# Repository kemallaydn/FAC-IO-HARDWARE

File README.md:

# FAC-IO Mini V1 — Ethernet Barrier Relay Controller

Status: **Integrated engineering draft. NOT production-ready.** KiCad 10.0.8 ERC/DRC and schematic parity currently pass; sourcing, mechanical, supplier, independent review, and first-article gates remain open.

FAC-IO is an Ethernet-connected, programmable dry-contact relay controller for integration with our own license-plate recognition/access-control software. It is **not** a barrier motor driver.

## V1 scope
- ESP32-C3-WROOM-02-N4 in current DRAFT BOM (GPIO/USB and antenna placement still require physical review)
- WIZnet WIZ850io (W5500 + PHY + magnetics + RJ45) as a plug-in module on two host sockets
- 2 independent, normally-open / common / normally-closed dry-contact relay outputs
- 12 V DC input, regulated 3.3 V logic supply
- USB programming/debug interface, BOOT/RESET recovery access
- Power, link and relay indicators; four mounting holes
- Firmware source contains DHCP and an HMAC-authenticated fixed-pulse command path; a host signer/client exists, but LPR integration, Secure Boot/flash-encryption production build and target verification are incomplete, so command service remains fail-closed in the current build
- Two independent hardware one-shots nominally limit OPEN/CLOSE relay pulses to about 503 ms; tolerance and fail-safe behavior still require first-article validation
- Optional future PoE; **not included** in V1
- RS232, RS485 and legacy Nöron protocol **not required** in V1

## System flow
LPR service -> authenticated LAN command -> FAC-IO -> timed dry-contact closure -> barrier controller OPEN or CLOSE input.

The dry-contact output must be wired only to the barrier controller's documented command input, **never directly to the motor or mains**. Each channel uses a fixed hardware one-shot (about 503 ms nominal from the current timer/resistor values); firmware cannot extend or configure the relay pulse. The full pulse tolerance and first-article maximum still require verification.

Hikvision's 42-Series brochure identifies the third-party command interfaces as **Rising Control ±** and **Falling Control ±**; it does not substantiate controller terminal numbers such as J4/J5. Wire each isolated relay COM/NO pair only across the matching, physically labelled command pair. Hikvision states that closing accepts pulsed signals only and a continuous closing signal can lock the barrier. The independent hardware one-shot bounds both outputs, but the nominal 503 ms pulse and its maximum tolerance must be verified on the exact controller revision before connection. Do not connect FAC-IO power or ground to these pairs. Never connect to mains, motor or traffic-light terminals. ([Hikvision 42-Series brochure](https://www.hikvision.com/content/dam/hikvision/en/brochures-download/product-brochures/Leaflet--Barrier-Gate-42-Series.pdf))

## Repository layout
- `docs/requirements.md`: engineering requirements and open decisions
- `docs/validation.md`: verification and acceptance plan
- `hardware/`: integrated KiCad schematic, PCB and local footprints
- `manufacturing/`: draft Gerber, Excellon, BOM, positions and validation artifacts
- `firmware/`: ESP32-C3/W5500 candidate firmware, protocol/security implementation and host tests; development target build passes, while production-secure build and first-article validation remain open

## Manufacturing release rule
The current-source bare-board review bundle is `manufacturing/REVIEW-2026-11-10-DRAFT/`; it contains fresh Gerber/Excellon outputs, current ERC/DRC reports, a preview and hashes. It includes `release/NOT-APPROVED.txt` and is not approved for fabrication. The package gate with `--root` currently reports only the missing independent approval file. CAM/stackup and drill/slot acceptance, Robotistan pricing/acceptance, module/header fit, independent electrical review and first-article tests remain open. `manufacturing/release_check.py` is the release gate.

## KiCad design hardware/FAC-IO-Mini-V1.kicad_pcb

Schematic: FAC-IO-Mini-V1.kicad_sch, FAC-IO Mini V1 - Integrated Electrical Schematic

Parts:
C1: 22uF/50V; C_1210_3225Metric; MPN C3225X7R1H226M250AC
C2: 10uF/50V; C_1206_3216Metric; MPN CGA5L1X7R1H106K160AC
C3: 100nF/50V; C_0603_1608Metric; MPN CC0603JRX7R9BB104
C4, C5: 22uF/10V; C_0805_2012Metric; MPN GRM21BZ71A226ME15L
C6: 1uF; C_0805_2012Metric; MPN GRM21BR71C105KA01L
C7: 10uF; C_0805_2012Metric; MPN GRM21BZ71E106KE15L
C8, C30: 100nF; C_0603_1608Metric; MPN CC0603JRX7R9BB104
C9: 1nF/2kV; C_1206_3216Metric; MPN CC1206KKX7RDBB102
C28, C29: 100nF/100V; C_0805_2012Metric; MPN C0805C104K1RACAUTO
D1: SS34; D_SMA; MPN B340A-13-F
D2: SMCJ15A-13-F; D_SMC; MPN SMCJ15A-13-F
D3, D4: 1N4007G; D_DO-41_SOD81_P10.16mm_Horizontal; MPN 1N4007G-T
F1: 1812L075/33DR; Fuse_1812_4532Metric; MPN 1812L075/33DR
J1: TB007-508-02BE; TerminalBlock_CUI_TB007-508-02_1x02_P5.08mm_Horizontal; MPN TB007-508-02BE
J2: TYPE-C-31-M-12; USB_C_Receptacle_HRO_TYPE-C-31-M-12; MPN TYPE-C-31-M-12
J4, J5: TB007-508-03BE; TerminalBlock_CUI_TB007-508-03_1x03_P5.08mm_Horizontal; MPN TB007-508-03BE
J6: SSQ-106-03-G-S; WIZ850io_Host_J1_Socket_1x06; MPN SSQ-106-03-G-S
J7: SSQ-106-03-G-S; WIZ850io_Host_J2_Socket_1x06; MPN SSQ-106-03-G-S
K1, K2: G6K-2P-Y DC12; Relay_DPDT_Omron_G6K-2P-Y; MPN G6K-2P-Y DC12
L1: XAL5050-472MEC; L_Coilcraft_XAL5050-XXX; MPN XAL5050-472MEC
PWR1, PWR2, PWR3, PWR5: PWR_FLAG
Q1, Q2: AO3400A; SOT-23; MPN AO3400A
R1, R2, R10, R11, R12: 10k; R_0603_1608Metric; MPN RC0603FR-0710KL
R3, R4: 5.1k; R_0603_1608Metric; MPN RC0603FR-075K1L
R5, R6: 22R; R_0603_1608Metric; MPN RC0603FR-0722RL
R7: 68k; R_0603_1608Metric; MPN RC0603FR-0768KL
R8, R20, R21, R26, R28: 100k; R_0603_1608Metric; MPN RC0603FR-07100KL
R23, R24: 768k; R_0603_1608Metric; MPN RC0603FR-07768KL
R25, R27: 1k; R_0603_1608Metric; MPN RC0603FR-071KL
R29: 1M; R_0603_1608Metric; MPN RC0603FR-071ML
R30: 523k; R_0603_1608Metric; MPN RC0603FR-07523KL
SW1: RESET; SW_SPST_TL3342; MPN TL3342F100QG
SW2: BOOT; SW_SPST_TL3342; MPN TL3342F100QG
U1: AP63203WU-7; TSOT-23-6; MPN AP63203WU-7
U2: ESP32-C3-WROOM-02-N4; ESP32-C3-WROOM-02_0p3mmThermal; MPN ESP32-C3-WROOM-02-N4
U3: USBLC6-2SC6; SOT-23-6; MPN USBLC6-2SC6
U5, U6: LTC6993IS6-1; TSOT-23-6; MPN LTC6993IS6-1#TRMPBF

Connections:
/3V3: C4.1, C5.1, C7.1, C8.1, C28.1, C29.1, C30.1, J7.2, J7.3, L1.2, PWR3.1, R1.1, R2.1, R10.1, R11.1, R12.1, R29.1, U1.1 (FB), U2.1 (3V3), U5.5 (V+), U6.5 (V+)
/12V_FUSED: D1.2 (A), F1.2
/12V_IN: F1.1, J1.1, PWR1.1
/12V_PROT: C1.1, C2.1, D1.1 (K), D2.1 (K), D3.1 (K), D4.1 (K), K1.A1, K2.A1, PWR2.1, U1.2 (EN), U1.3 (IN)
/BOOT_N: R2.2, SW2.1, U2.8 (IO9)
/BUCK_BST: C3.1, U1.6 (BST)
/BUCK_SW: C3.2, L1.1, U1.5 (SW)
/CHASSIS: C9.1, J2.SH (SHIELD)
/CLOSE_COM: J5.2, K2.11
/CLOSE_NC: J5.1, K2.12
/CLOSE_NO: J5.3, K2.14
/COIL1_LOW: D3.2 (A), K1.A2, Q1.3 (D)
/COIL2_LOW: D4.2 (A), K2.A2, Q2.3 (D)
/ESP_EN: C6.1, R1.2, SW1.1, U2.2 (EN)
/ETH_CS_N: J6.5, R10.2, U2.6 (IO7)
/ETH_INT_N: J6.6, R11.2, U2.10 (IO10)
/ETH_MISO: J7.6, U2.5 (IO6)
/ETH_MOSI: J6.3, U2.4 (IO5)
/ETH_RESET_N: J7.5, R12.2, U2.15 (IO3)
/ETH_SCK: J6.4, U2.3 (IO4)
/GATE1: Q1.1 (G), R25.2, R26.1
/GATE2: Q2.1 (G), R27.2, R28.1
/GND: C1.2, C2.2, C4.2, C5.2, C6.2, C7.2, C8.2, C9.2, C28.2, C29.2, C30.2, D2.2 (A), J1.2, J2.A1 (GND), J2.A12 (GND), J2.B1 (GND), J2.B12 (GND), J6.1, J6.2, J7.1, PWR5.1, Q1.2 (S), Q2.2 (S), R3.2, R4.2, R8.2, R20.2, R21.2, R23.2, R24.2, R26.2, R28.2, R30.2, SW1.2, SW2.2, U1.4 (GND), U2.9 (GND), U2.19 (GND), U3.2 (GND), U5.2 (GND), U6.2 (GND)
/OPEN_COM: J4.2, K1.11
/OPEN_NC: J4.1, K1.12
/OPEN_NO: J4.3, K1.14
/PULSE1: R25.1, U5.6 (OUT)
/PULSE2: R27.1, U6.6 (OUT)
/SET1: R23.1, U5.3 (SET)
/SET2: R24.1, U6.3 (SET)
/TIMER_DIV: R29.2, R30.1, U5.4 (DIV), U6.4 (DIV)
/TRIG1: R20.1, U2.18 (IO0), U5.1 (TRIG)
/TRIG2: R21.1, U2.17 (IO1), U6.1 (TRIG)
/USB_CC1: J2.A5 (CC1), R3.1
/USB_CC2: J2.B5 (CC2), R4.1
/USB_DM: R6.2, U2.13 (IO18)
/USB_DM_CONN: J2.A7 (D-), J2.B7 (D-), R6.1, U3.3 (I/O2), U3.4 (I/O2)
/USB_DP: R5.2, U2.14 (IO19)
/USB_DP_CONN: J2.A6 (D+), J2.B6 (D+), R5.1, U3.1 (I/O1), U3.6 (I/O1)
/USB_VBUS: J2.A4 (VBUS), J2.A9 (VBUS), J2.B4 (VBUS), J2.B9 (VBUS), R7.1, U3.5 (VBUS)
/USB_VBUS_SENSE: R7.2, R8.1, U2.12 (IO21/TXD)

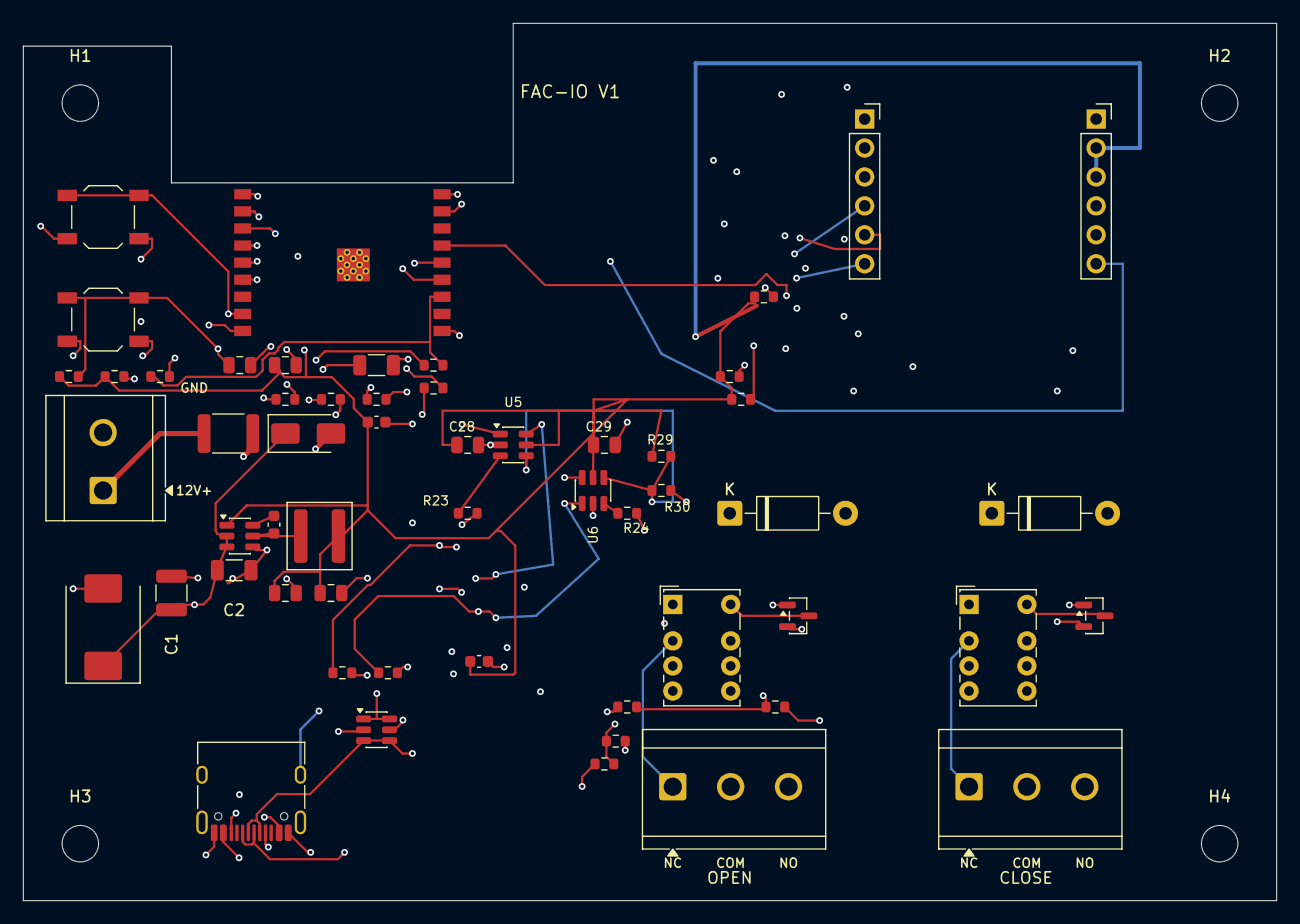
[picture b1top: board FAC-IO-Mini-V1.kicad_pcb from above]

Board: 4 copper layers, 110.0 x 77.0 mm, 60 parts (0 on the bottom side), 41 nets.

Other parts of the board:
H1, H2, H3, H4: MountingHole_3.2mm_M3

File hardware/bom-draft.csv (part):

Reference,Quantity,Value,Footprint,Manufacturer MPN,RobotistanPro/LCSC C Code,Populate,Status
C1,1,22uF/50V,Capacitor_SMD:C_1210_3225Metric,C3225X7R1H226M250AC,,YES,TDK 22uF/50V X7R 1210; input-bank DC-bias/temp/tolerance calculation and supplier availability remain to confirm
C2,1,10uF/50V,Capacitor_SMD:C_1206_3216Metric,CGA5L1X7R1H106K160AC,,YES,TDK 10uF/50V X7R 1206; input-bank DC-bias/temp/tolerance calculation and supplier availability remain to confirm
C3,1,100nF/50V,Capacitor_SMD:C_0603_1608Metric,C1608X7R1H104K080AA,C72453,YES,"TDK active-production 100nF 50V X7R 0603; LCSC C72453 matches exact MPN; supply, stock and assembly acceptance remain open"
C4,1,22uF/10V,Capacitor_SMD:C_0805_2012Metric,GRM21BZ71A226ME15L,C907991,YES,"LCSC code C907991 maps to exact manufacturer MPN GRM21BZ71A226ME15L; current stock, Robotistan procurement import and assembly acceptance remain unverified"
C5,1,22uF/10V,Capacitor_SMD:C_0805_2012Metric,GRM21BZ71A226ME15L,C907991,YES,"LCSC code C907991 maps to exact manufacturer MPN GRM21BZ71A226ME15L; current stock, Robotistan procurement import and assembly acceptance remain unverified"
C6,1,1uF,Capacitor_SMD:C_0805_2012Metric,GRM21BR71C105KA01L,C77079,YES,"LCSC code C77079 maps to exact manufacturer MPN GRM21BR71C105KA01L; current stock, Robotistan procurement import and assembly acceptance remain unverified"
C7,1,10uF,Capacitor_SMD:C_0805_2012Metric,GRM21BZ71E106KE15L,C237493,YES,"LCSC code C237493 maps to exact manufacturer MPN GRM21BZ71E106KE15L; current stock, Robotistan procurement import and assembly acceptance remain unverified"
C8,1,100nF,Capacitor_SMD:C_0603_1608Metric,C1608X7R1H104K080AA,C72453,YES,"TDK active-production 100nF 50V X7R 0603; LCSC C72453 matches exact MPN; supply, stock and assembly acceptance remain open"
C9,1,1nF/2kV,Capacitor_SMD:C_1206_3216Metric,C1206C102KGRACTU,C479755,YES,"LCSC code C479755 maps to exact manufacturer MPN C1206C102KGRACTU; current stock, Robotistan procurement import and assembly acceptance remain unverified"
C28,1,100nF/100V,Capacitor_SMD:C_0805_2012Metric,C2012X7R2A104K125AA,C2167715,YES,"LCSC code C2167715 maps to exact manufacturer MPN C2012X7R2A104K125AA; current stock, Robotistan procurement import and assembly acceptance remain unverified"
C29,1,100nF/100V,Capacitor_SMD:C_0805_2012Metric,C2012X7R2A104K125AA,C2167715,YES,"LCSC code C2167715 maps to exact manufacturer MPN C2012X7R2A104K125AA; current stock, Robotistan procurement import and assembly acceptance remain unverified"
C30,1,100nF,Capacitor_SMD:C_0603_1608Metric,C1608X7R1H104K080AA,C72453,YES,"TDK active-production 100nF 50V X7R 0603; LCSC C72453 matches exact MPN; supply, stock and assembly acceptance remain open"
D1,1,SS34,Diode_SMD:D_SMA,B340A-13-F,C85098,YES,"LCSC code C85098 maps to exact manufacturer MPN B340A-13-F; current stock, Robotistan procurement import and assembly acceptance remain unverified"
D2,1,SMCJ15A-13-F,Diode_SMD:D_SMC,SMCJ15A-13-F,C135138,YES,"LCSC C135138 maps to exact Diodes Incorporated MPN SMCJ15A-13-F; procurement import, current stock and assembly acceptance remain unverified"
D3,1,1N4007G,Diode_THT:D_DO-41_SOD81_P10.16mm_Horizontal,1N4007G-T,C516593,YES,"LCSC code C516593 maps to exact manufacturer MPN 1N4007G-T; current stock, Robotistan procurement import and assembly acceptance remain unverified"
D4,1,1N4007G,Diode_THT:D_DO-41_SOD81_P10.16mm_Horizontal,1N4007G-T,C516593,YES,"LCSC code C516593 maps to exact manufacturer MPN 1N4007G-T; current stock, Robotistan procurement import and assembly acceptance remain unverified"
F1,1,1812L075/33DR,Fuse:Fuse_1812_4532Metric,1812L075/33DR,C151170,YES,LCSC C151170 maps to exact Littelfuse MPN 1812L075/33DR; catalog stock/import listing is not Robotistan procurement confirmation; thermal/load validation remains open
J1,1,TB007-508-02BE,TerminalBlock_CUI:TerminalBlock_CUI_TB007-508-02_1x02_P5.08mm_Horizontal,TB007-508-02BE,C3816270,YES,"Exact CUI TB007-508-02BE catalog code C3816270; Robotistan purchase/import, stock and assembly acceptance remain open"
J2,1,TYPE-C-31-M-12,Connector_USB:USB_C_Receptacle_HRO_TYPE-C-31-M-12,TYPE-C-31-M-12,C165948,YES,"LCSC C165948 maps to exact HRO MPN TYPE-C-31-M-12; procurement import, current stock and assembly acceptance remain unverified"
J4,1,TB007-508-03BE,TerminalBlock_CUI:TerminalBlock_CUI_TB007-508-03_1x03_P5.08mm_Horizontal,TB007-508-03BE,C3820511,YES,"Exact CUI TB007-508-03BE catalog code C3820511; Robotistan purchase/import, stock and assembly acceptance remain open"
J5,1,TB007-508-03BE,TerminalBlock_CUI:TerminalBlock_CUI_TB007-508-03_1x03_P5.08mm_Horizontal,TB007-508-03BE,C3820511,YES,"Exact CUI TB007-508-03BE catalog code C3820511; Robotistan purchase/import, stock and assembly acceptance remain open"
J6,1,SSQ-106-03-G-S,FAC_IO:WIZ850io_Host_J1_Socket_1x06,SSQ-106-03-G-S,C3323798,YES,"LCSC C3323798 maps to exact Samtec MPN SSQ-106-03-G-S; procurement import, current stock, mating and assembly acceptance remain unverified"
J7,1,SSQ-106-03-G-S,FAC_IO:WIZ850io_Host_J2_Socket_1x06,SSQ-106-03-G-S,C3323798,YES,"LCSC C3323798 maps to exact Samtec MPN SSQ-106-03-G-S; procurement import, current stock, mating and assembly acceptance remain unverified"
K1,1,G6K-2P-Y DC12,Relay_THT:Relay_DPDT_Omron_G6K-2P-Y,G6K-2P-Y DC12,C132367,YES,"LCSC C132367 maps to exact manufacturer MPN G6K-2P-Y DC12; Robotistan import, current stock, procurement and assembly acceptance remain unverified"
K2,1,G6K-2P-Y DC12,Relay_THT:Relay_DPDT_Omron_G6K-2P-Y,G6K-2P-Y DC12,C132367,YES,"LCSC C132367 maps to exact manufacturer MPN G6K-2P-Y DC12; Robotistan import, current stock, procurement and assembly acceptance remain unverified"
L1,1,XAL5050-472MEC,Inductor_SMD:L_Coilcraft_XAL5050-XXX,XAL5050-472MEC,,YES,"MPN matched to schematic; Robotistan purchase code, stock and assembly acceptance open"
Q1,1,AO3400A,Package_TO_SOT_SMD:SOT-23,AO3400A,C20917,YES,"LCSC code C20917 maps to exact manufacturer MPN AO3400A; current stock, Robotistan procurement import and assembly acceptance remain unverified"
Q2,1,AO3400A,Package_TO_SOT_SMD:SOT-23,AO3400A,C20917,YES,"LCSC code C20917 maps to exact manufacturer MPN AO3400A; current stock, Robotistan procurement import and assembly acceptance remain unverified"
R1,1,10k,Resistor_SMD:R_0603_1608Metric,RC0603FR-0710KL,C98220,YES,"LCSC code C98220 maps to exact RC0603FR-0710KL 0603 YAGEO part; current stock, Robotistan procurement import and assembly acceptance remain unverified"
R2,1,10k,Resistor_SMD:R_0603_1608Metric,RC0603FR-0710KL,C98220,YES,"LCSC code C98220 maps to exact RC0603FR-0710KL 0603 YAGEO part; current stock, Robotistan procurement import and assembly acceptance remain unverified"
R3,1,5.1k,Resistor_SMD:R_0603_1608Metric,RC0603FR-075K1L,C105580,YES,"LCSC code C105580 maps to exact RC0603FR-075K1L 0603 YAGEO part; current stock, Robotistan procurement import and assembly acceptance remain unverified"
R4,1,5.1k,Resistor_SMD:R_0603_1608Metric,RC0603FR-075K1L,C105580,YES,"LCSC code C105580 maps to exact RC0603FR-075K1L 0603 YAGEO part; current stock, Robotistan procurement import and assembly acceptance remain unverified"
R5,1,22R,Resistor_SMD:R_0603_1608Metric,RC0603FR-0722RL,C107701,YES,"LCSC code C107701 maps to exact RC0603FR-0722RL 0603 YAGEO part; current stock, Robotistan procurement import and assembly acceptance remain unverified"
R6,1,22R,Resistor_SMD:R_0603_1608Metric,RC0603FR-0722RL,C107701,YES,"LCSC code C107701 maps to exact RC0603FR-0722RL 0603 YAGEO part; current stock, Robotistan procurement import and assembly acceptance remain unverified"
R7,1,68k,Resistor_SMD:R_0603_1608Metric,RC0603FR-0768KL,C114633,YES,"LCSC code C114633 maps to exact RC0603FR-0768KL 0603 YAGEO part; current stock, Robotistan procurement import and assembly acceptance remain unverified"
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
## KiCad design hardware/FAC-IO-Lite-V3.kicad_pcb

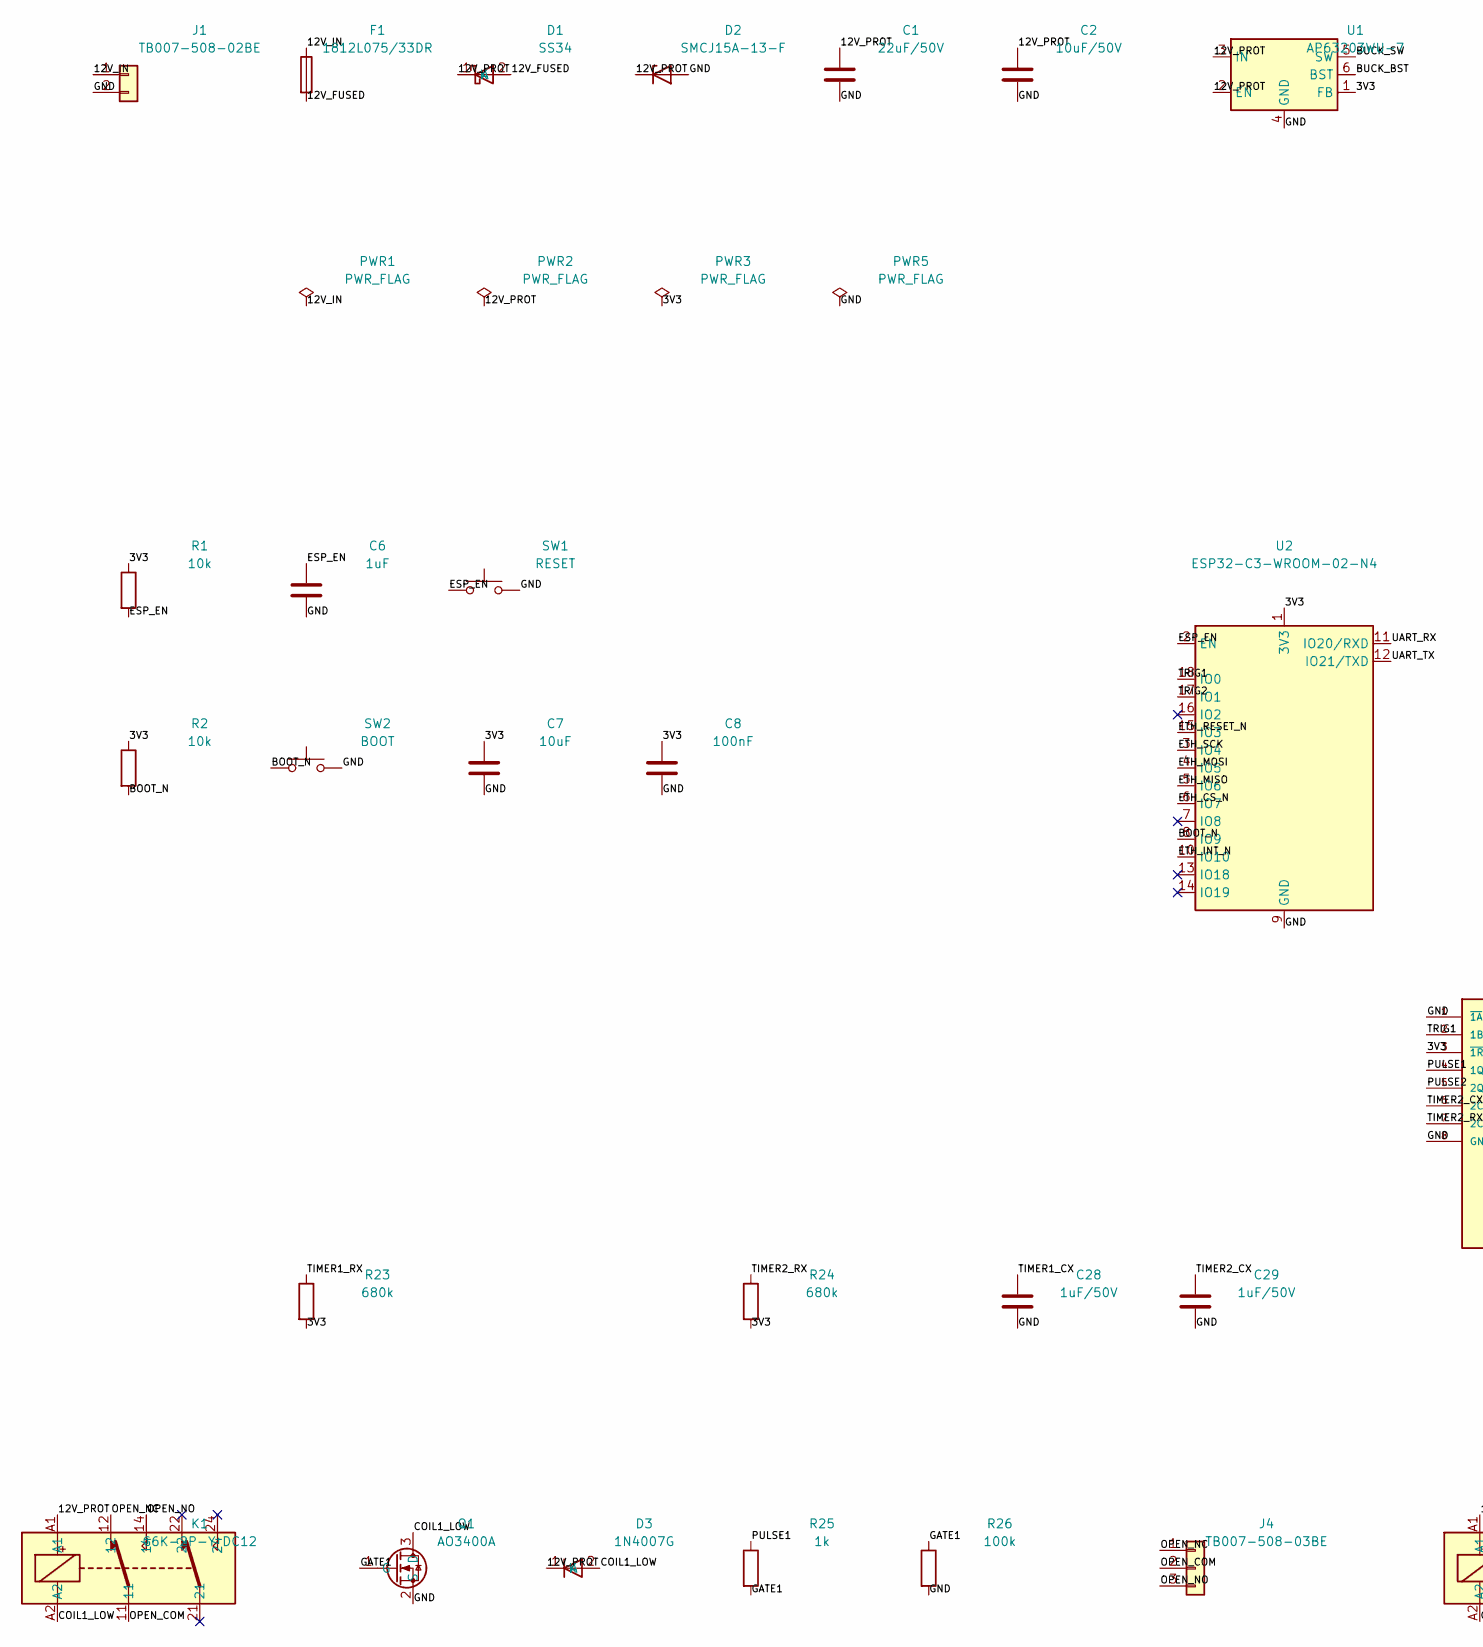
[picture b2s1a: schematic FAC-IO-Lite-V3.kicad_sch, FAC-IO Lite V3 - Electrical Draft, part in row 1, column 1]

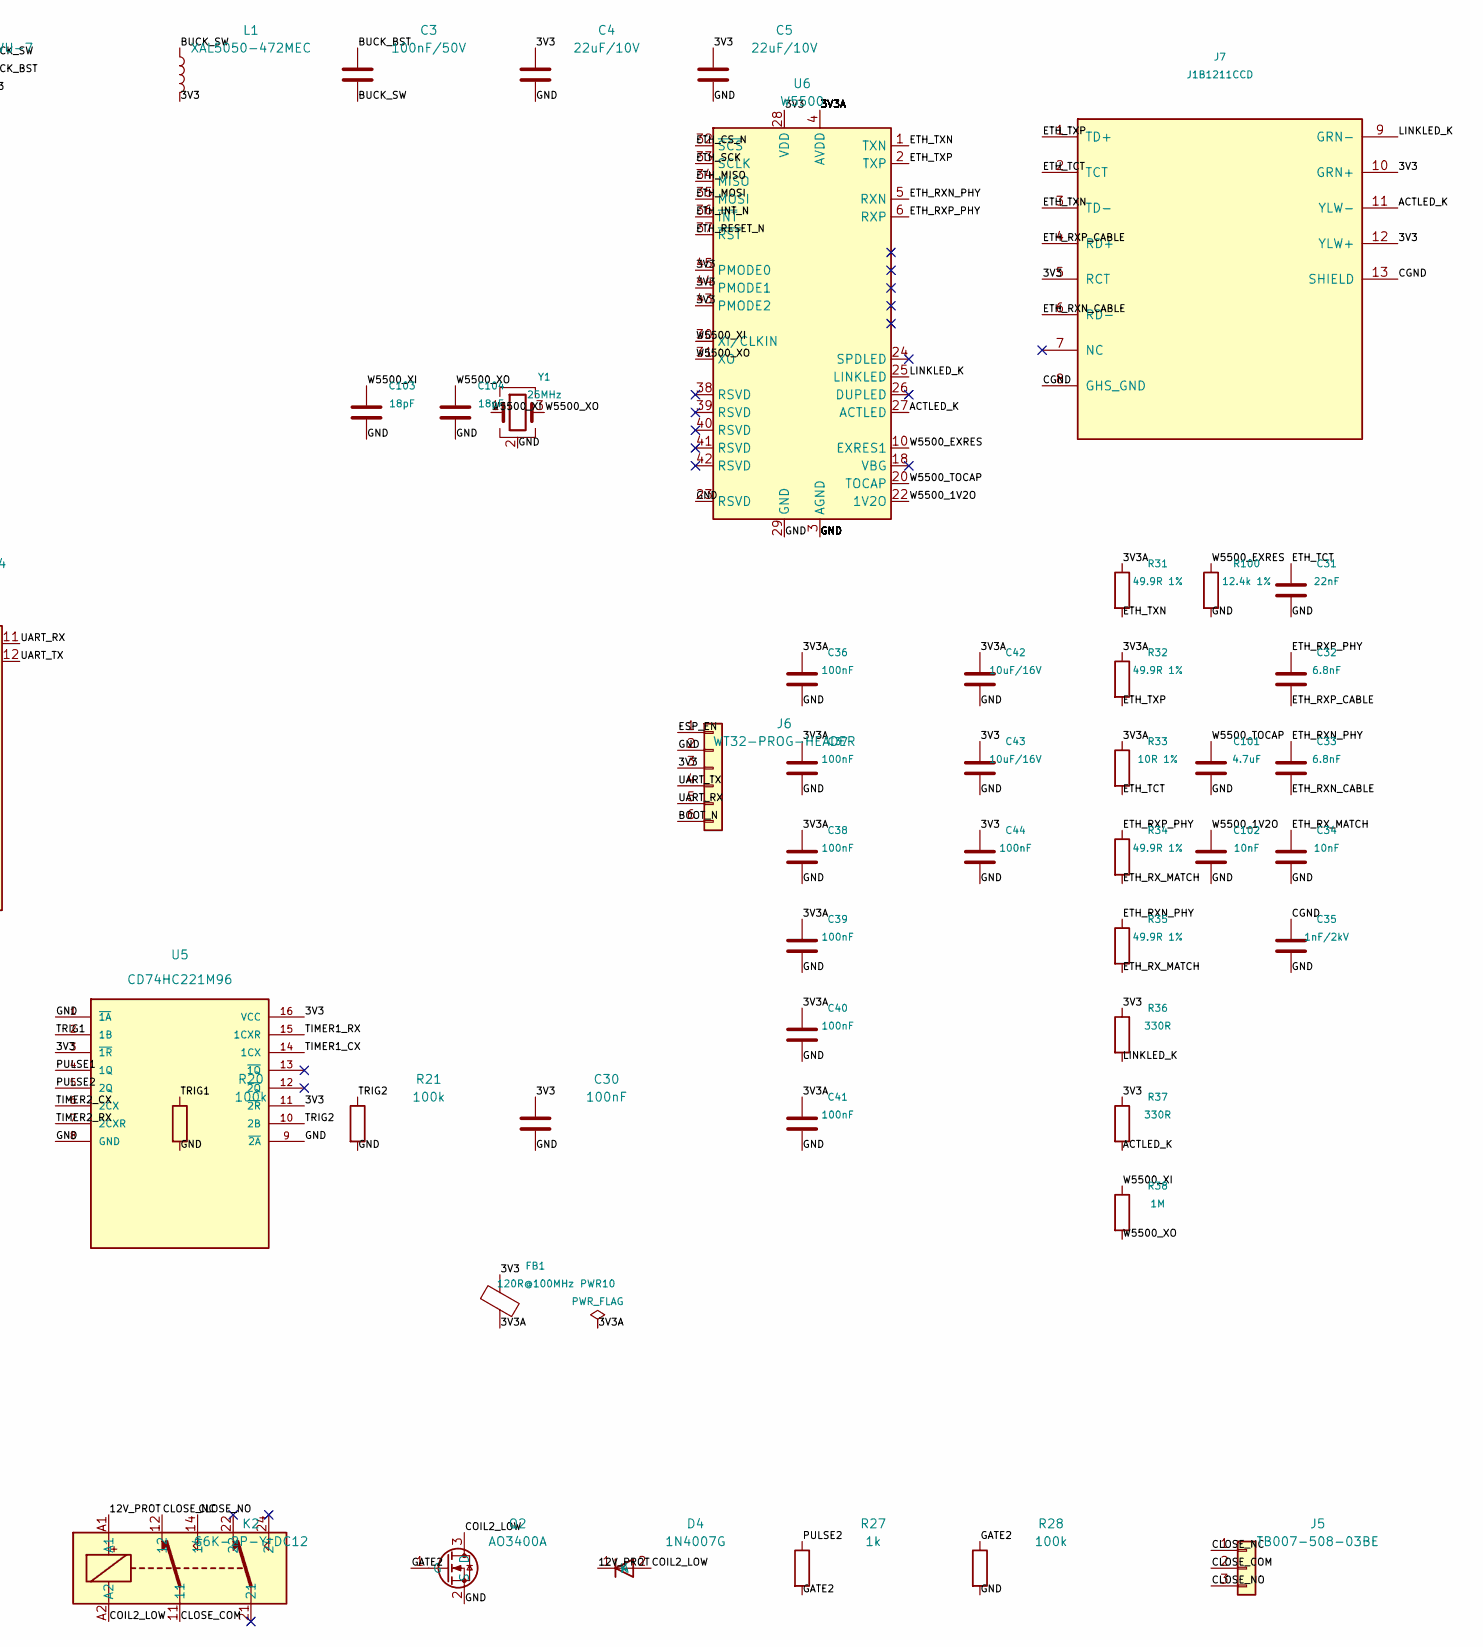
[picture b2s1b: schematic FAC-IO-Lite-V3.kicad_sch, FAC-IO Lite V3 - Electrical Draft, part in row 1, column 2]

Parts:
C1: 22uF/50V; C_1210_3225Metric; MPN C3225X7R1H226M250AC
C2: 10uF/50V; C_1206_3216Metric; MPN CGA5L1X7R1H106K160AC
C3: 100nF/50V; C_0603_1608Metric; MPN CC0603JRX7R9BB104
C4, C5: 22uF/10V; C_0805_2012Metric; MPN GRM21BZ71A226ME15L
C6: 1uF; C_0805_2012Metric; MPN GRM21BR71C105KA01L
C7: 10uF; C_0805_2012Metric; MPN GRM21BZ71E106KE15L
C8, C30: 100nF; C_0603_1608Metric; MPN CC0603JRX7R9BB104
C28, C29: 1uF/50V; C_0805_2012Metric; MPN C0805C105K5RACTU
C31: 22nF; C_0603_1608Metric
C32, C33: 6.8nF; C_0603_1608Metric
C34, C102: 10nF; C_0603_1608Metric
C35: 1nF/2kV; C_1206_3216Metric
C36, C37, C38, C39, C40, C41, C44: 100nF; C_0603_1608Metric
C42, C43: 10uF/16V; C_0805_2012Metric
C101: 4.7uF; C_0805_2012Metric
C103, C104: 18pF; C_0603_1608Metric
D1: SS34; D_SMA; MPN B340A-13-F
D2: SMCJ15A-13-F; D_SMC; MPN SMCJ15A-13-F
D3, D4: 1N4007G; D_DO-41_SOD81_P10.16mm_Horizontal; MPN 1N4007G-T
F1: 1812L075/33DR; Fuse_1812_4532Metric; MPN 1812L075/33DR
FB1: 120R@100MHz; L_0603_1608Metric; MPN HHM1M1608-121JT
J1: TB007-508-02BE; TerminalBlock_CUI_TB007-508-02_1x02_P5.08mm_Horizontal; MPN TB007-508-02BE
J4, J5: TB007-508-03BE; TerminalBlock_CUI_TB007-508-03_1x03_P5.08mm_Horizontal; MPN TB007-508-03BE
J6: WT32-PROG-HEADER; PinHeader_1x06_P2.54mm_Vertical; MPN TBD_STANDARD_1X06_HEADER
J7: J1B1211CCD; RJ45_Cetus_J1B1211CCD_Horizontal; MPN J1B1211CCD
K1, K2: G6K-2P-Y DC12; Relay_DPDT_Omron_G6K-2P-Y; MPN G6K-2P-Y DC12
L1: XAL5050-472MEC; L_Coilcraft_XAL5050-XXX; MPN XAL5050-472MEC
PWR1, PWR2, PWR3, PWR5, PWR10: PWR_FLAG
Q1, Q2: AO3400A; SOT-23; MPN AO3400A
R1, R2: 10k; R_0603_1608Metric; MPN RC0603FR-0710KL
R20, R21, R26, R28: 100k; R_0603_1608Metric; MPN RC0603FR-07100KL
R23, R24: 680k; R_0603_1608Metric; MPN RC0603FR-07680KL
R25, R27: 1k; R_0603_1608Metric; MPN RC0603FR-071KL
R31, R32, R34, R35: 49.9R 1%; R_0603_1608Metric
R33: 10R 1%; R_0603_1608Metric
R36, R37: 330R; R_0603_1608Metric
R38: 1M; R_0603_1608Metric; MPN RC0603FR-071ML
R100: 12.4k 1%; R_0603_1608Metric; MPN RC0603FR-0712K4L
SW1: RESET; SW_SPST_TL3342; MPN TL3342F100QG
SW2: BOOT; SW_SPST_TL3342; MPN TL3342F100QG
U1: AP63203WU-7; TSOT-23-6; MPN AP63203WU-7
U2: ESP32-C3-WROOM-02-N4; ESP32-C3-WROOM-02_0p3mmThermal; MPN ESP32-C3-WROOM-02-N4
U5: CD74HC221M96; SOIC-16_3.9x9.9mm_P1.27mm; MPN CD74HC221M96; LCSC C133954
U6: W5500; LQFP-48_7x7mm_P0.5mm; MPN W5500
Y1: 25MHz; Crystal_SMD_3225-4Pin_3.2x2.5mm; MPN TBD_25MHZ_CRYSTAL

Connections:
/3V3: C4.1, C5.1, C7.1, C8.1, C30.1, C43.1, C44.1, FB1.1, J6.3, J7.5 (RCT), J7.10 (GRN+), J7.12 (YLW+), L1.2, PWR3.1, R1.1, R2.1, R23.2, R24.2, R36.1, R37.1, U1.1 (FB), U2.1 (3V3), U5.3 (~1R), U5.11 (~2R), U5.16 (VCC), U6.28 (VDD), U6.43 (PMODE2), U6.44 (PMODE1), U6.45 (PMODE0)
/3V3A: C36.1, C37.1, C38.1, C39.1, C40.1, C41.1, C42.1, FB1.2, PWR10.1, R31.1, R32.1, R33.1, U6.4 (AVDD), U6.8 (AVDD), U6.11 (AVDD), U6.15 (AVDD), U6.17 (AVDD), U6.21 (AVDD)
/12V_FUSED: D1.2 (A), F1.2
/12V_IN: F1.1, J1.1, PWR1.1
/12V_PROT: C1.1, C2.1, D1.1 (K), D2.1 (K), D3.1 (K), D4.1 (K), K1.A1, K2.A1, PWR2.1, U1.2 (EN), U1.3 (IN)
/ACTLED_K: J7.11 (YLW-), R37.2, U6.27 (ACTLED)
/BOOT_N: J6.6, R2.2, SW2.1, U2.8 (IO9)
/BUCK_BST: C3.1, U1.6 (BST)
/BUCK_SW: C3.2, L1.1, U1.5 (SW)
/CGND: C35.1, J7.8 (GHS_GND), J7.13 (SHIELD)
/CLOSE_COM: J5.2, K2.11
/CLOSE_NC: J5.1, K2.12
/CLOSE_NO: J5.3, K2.14
/COIL1_LOW: D3.2 (A), K1.A2, Q1.3 (D)
/COIL2_LOW: D4.2 (A), K2.A2, Q2.3 (D)
/ESP_EN: C6.1, J6.1, R1.2, SW1.1, U2.2 (EN)
/ETH_CS_N: U2.6 (IO7), U6.32 (~SCS)
/ETH_INT_N: U2.10 (IO10), U6.36 (~INT)
/ETH_MISO: U2.5 (IO6), U6.34 (MISO)
/ETH_MOSI: U2.4 (IO5), U6.35 (MOSI)
/ETH_RESET_N: U2.15 (IO3), U6.37 (~RST)
/ETH_RXN_CABLE: C33.2, J7.6 (RD-)
/ETH_RXN_PHY: C33.1, R35.1, U6.5 (RXN)
/ETH_RXP_CABLE: C32.2, J7.4 (RD+)
/ETH_RXP_PHY: C32.1, R34.1, U6.6 (RXP)
/ETH_RX_MATCH: C34.1, R34.2, R35.2
/ETH_SCK: U2.3 (IO4), U6.33 (SCLK)
/ETH_TCT: C31.1, J7.2 (TCT), R33.2
/ETH_TXN: J7.3 (TD-), R31.2, U6.1 (TXN)
/ETH_TXP: J7.1 (TD+), R32.2, U6.2 (TXP)
/GATE1: Q1.1 (G), R25.2, R26.1
/GATE2: Q2.1 (G), R27.2, R28.1
/GND: C1.2, C2.2, C4.2, C5.2, C6.2, C7.2, C8.2, C28.2, C29.2, C30.2, C31.2, C34.2, C35.2, C36.2, C37.2, C38.2, C39.2, C40.2, C41.2, C42.2, C43.2, C44.2, C101.2, C102.2, C103.2, C104.2, D2.2 (A), J1.2, J6.2, PWR5.1, Q1.2 (S), Q2.2 (S), R20.2, R21.2, R26.2, R28.2, R100.2, SW1.2, SW2.2, U1.4 (GND), U2.9 (GND), U2.19 (GND), U5.1 (~1A), U5.8 (GND), U5.9 (~2A), U6.3 (AGND), U6.9 (AGND), U6.14 (AGND), U6.16 (AGND), U6.19 (AGND), U6.23 (RSVD), U6.29 (GND), U6.48 (AGND), Y1.2 (G), Y1.4 (G)
/LINKLED_K: J7.9 (GRN-), R36.2, U6.25 (LINKLED)
/OPEN_COM: J4.2, K1.11
/OPEN_NC: J4.1, K1.12
/OPEN_NO: J4.3, K1.14
/PULSE1: R25.1, U5.4 (1Q)
/PULSE2: R27.1, U5.5 (2Q)
/TIMER1_CX: C28.1, U5.14 (1CX)
/TIMER1_RX: R23.1, U5.15 (1CXR)
/TIMER2_CX: C29.1, U5.6 (2CX)
/TIMER2_RX: R24.1, U5.7 (2CXR)
/TRIG1: R20.1, U2.18 (IO0), U5.2 (1B)
/TRIG2: R21.1, U2.17 (IO1), U5.10 (2B)
/UART_RX: J6.5, U2.11 (IO20/RXD)
/UART_TX: J6.4, U2.12 (IO21/TXD)
/W5500_1V2O: C102.1, U6.22 (1V2O)
/W5500_EXRES: R100.1, U6.10 (EXRES1)
/W5500_TOCAP: C101.1, U6.20 (TOCAP)
/W5500_XI: C103.1, R38.1, U6.30 (XI/CLKIN), Y1.1
/W5500_XO: C104.1, R38.2, U6.31 (XO), Y1.3

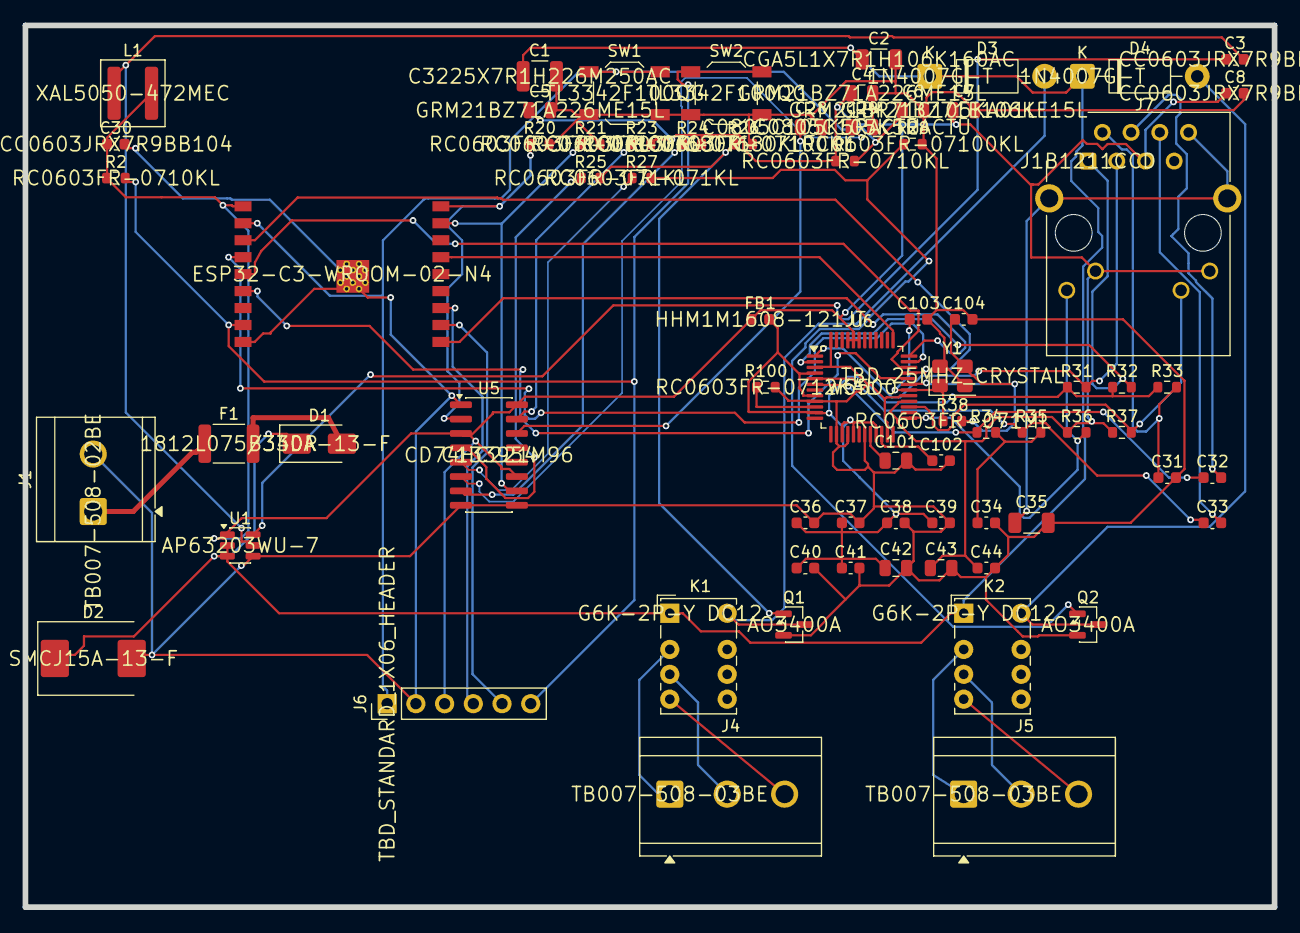
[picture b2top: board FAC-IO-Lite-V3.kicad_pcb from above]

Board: 2 copper layers, 110.5 x 78.0 mm, 71 parts (0 on the bottom side), 52 nets.

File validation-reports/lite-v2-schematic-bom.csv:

"Refs","Value","Footprint","Qty","DNP"
"C1","22uF/50V","Capacitor_SMD:C_1210_3225Metric","1",""
"C2","10uF/50V","Capacitor_SMD:C_1206_3216Metric","1",""
"C3","100nF/50V","Capacitor_SMD:C_0603_1608Metric","1",""
"C4","22uF/10V","Capacitor_SMD:C_0805_2012Metric","1",""
"C5","22uF/10V","Capacitor_SMD:C_0805_2012Metric","1",""
"C6","1uF","Capacitor_SMD:C_0805_2012Metric","1",""
"C7","10uF","Capacitor_SMD:C_0805_2012Metric","1",""
"C8","100nF","Capacitor_SMD:C_0603_1608Metric","1",""
"C28","1uF/50V","Capacitor_SMD:C_0805_2012Metric","1",""
"C29","1uF/50V","Capacitor_SMD:C_0805_2012Metric","1",""
"C30","100nF","Capacitor_SMD:C_0603_1608Metric","1",""
"D1","SS34","Diode_SMD:D_SMA","1",""
"D2","SMCJ15A-13-F","Diode_SMD:D_SMC","1",""
"D3","1N4007G","Diode_THT:D_DO-41_SOD81_P10.16mm_Horizontal","1",""
"D4","1N4007G","Diode_THT:D_DO-41_SOD81_P10.16mm_Horizontal","1",""
"F1","1812L075/33DR","Fuse:Fuse_1812_4532Metric","1",""
"J1","TB007-508-02BE","TerminalBlock_CUI:TerminalBlock_CUI_TB007-508-02_1x02_P5.08mm_Horizontal","1",""
"J4","TB007-508-03BE","TerminalBlock_CUI:TerminalBlock_CUI_TB007-508-03_1x03_P5.08mm_Horizontal","1",""
"J5","TB007-508-03BE","TerminalBlock_CUI:TerminalBlock_CUI_TB007-508-03_1x03_P5.08mm_Horizontal","1",""
"J6","WT32-PROG-HEADER","Connector_PinHeader_2.54mm:PinHeader_1x06_P2.54mm_Vertical","1",""
"K1","G6K-2P-Y DC12","Relay_THT:Relay_DPDT_Omron_G6K-2P-Y","1",""
"K2","G6K-2P-Y DC12","Relay_THT:Relay_DPDT_Omron_G6K-2P-Y","1",""
"L1","XAL5050-472MEC","Inductor_SMD:L_Coilcraft_XAL5050-XXX","1",""
"Q1","AO3400A","Package_TO_SOT_SMD:SOT-23","1",""
"Q2","AO3400A","Package_TO_SOT_SMD:SOT-23","1",""
"R1","10k","Resistor_SMD:R_0603_1608Metric","1",""
"R2","10k","Resistor_SMD:R_0603_1608Metric","1",""
"R20","100k","Resistor_SMD:R_0603_1608Metric","1",""
"R21","100k","Resistor_SMD:R_0603_1608Metric","1",""
"R23","680k","Resistor_SMD:R_0603_1608Metric","1",""
"R24","680k","Resistor_SMD:R_0603_1608Metric","1",""
"R25","1k","Resistor_SMD:R_0603_1608Metric","1",""
"R26","100k","Resistor_SMD:R_0603_1608Metric","1",""
"R27","1k","Resistor_SMD:R_0603_1608Metric","1",""
"R28","100k","Resistor_SMD:R_0603_1608Metric","1",""
"SW1","RESET","Button_Switch_SMD:SW_SPST_TL3342","1",""
"SW2","BOOT","Button_Switch_SMD:SW_SPST_TL3342","1",""
"U1","AP63203WU-7","Package_TO_SOT_SMD:TSOT-23-6","1",""
"U2","WT32-ETH01","","1",""
"U5","CD74HC221M96","Package_SO:SOIC-16_3.9x9.9mm_P1.27mm","1",""
